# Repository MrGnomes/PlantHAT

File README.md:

<meta name='keywords' content='plantHAT, HAT, raspberry pi HAT, pi, IoT, app, python, raspberry pi, plant, plants, watering, automated greenhouse, pi watering plants'>

# PlantHAT

Python library and design files for a modular plant monitoring and watering system based on the Raspberry Pi.

It is powered by a 12V power supply an it backpowers the Pi so that everything can be run from a single supply.
The 12V can be used to power up to 5 additional 12V inductive loads, like water pumps or magnetic valves that can be controlled over 
the GPIO Pins of the Pi.

# Sensors

Connect a 3 Wire temperature/humidity sensor (e.g. DHT22) and up to 4 I2C sensors to monitor your plants.

# Hardware

You can find the schematic design file in the "hardware" section of this repo.

## Maximum Ratings
The HAT is designed to work with a single power supply, that backpowers the raspberry pi with 5V/2A.

Input Voltage: 12V 

# Python3 Web-APP (Flask)

## Windows
The App was written using the current Python Tool for Visual Studio included in the community edition of Visual Studio 2017 and as an extension for Visual Studio 2015.
If you have the GitHub extension for Visual Studio and the python tools installed you can clone the git and start right away by using the solution file.

By using the Visual Studio as the IDE, the flask based WebApp can be compiled and debugged on the windows development PC.
When the code is working, the app can be run inside the Pi and by using the PTVSD package one can remotely debug the flask app directly from the VS-IDE by attaching to the running process using the IP-Address of the Pi.
Python 3.4 (32-bit) was used, because this was the current python version supported by the Pi, when I started the project.

## Linux

If you are using linux, just clone the repo, install the required packages and run the app by typing:
>> python3 run.py

inside the app folder.

(requirements.txt file is coming soon)

## Screenshot

This is what the current working App looks like:

# Coming Soon - Sensor data charts and GPIO control

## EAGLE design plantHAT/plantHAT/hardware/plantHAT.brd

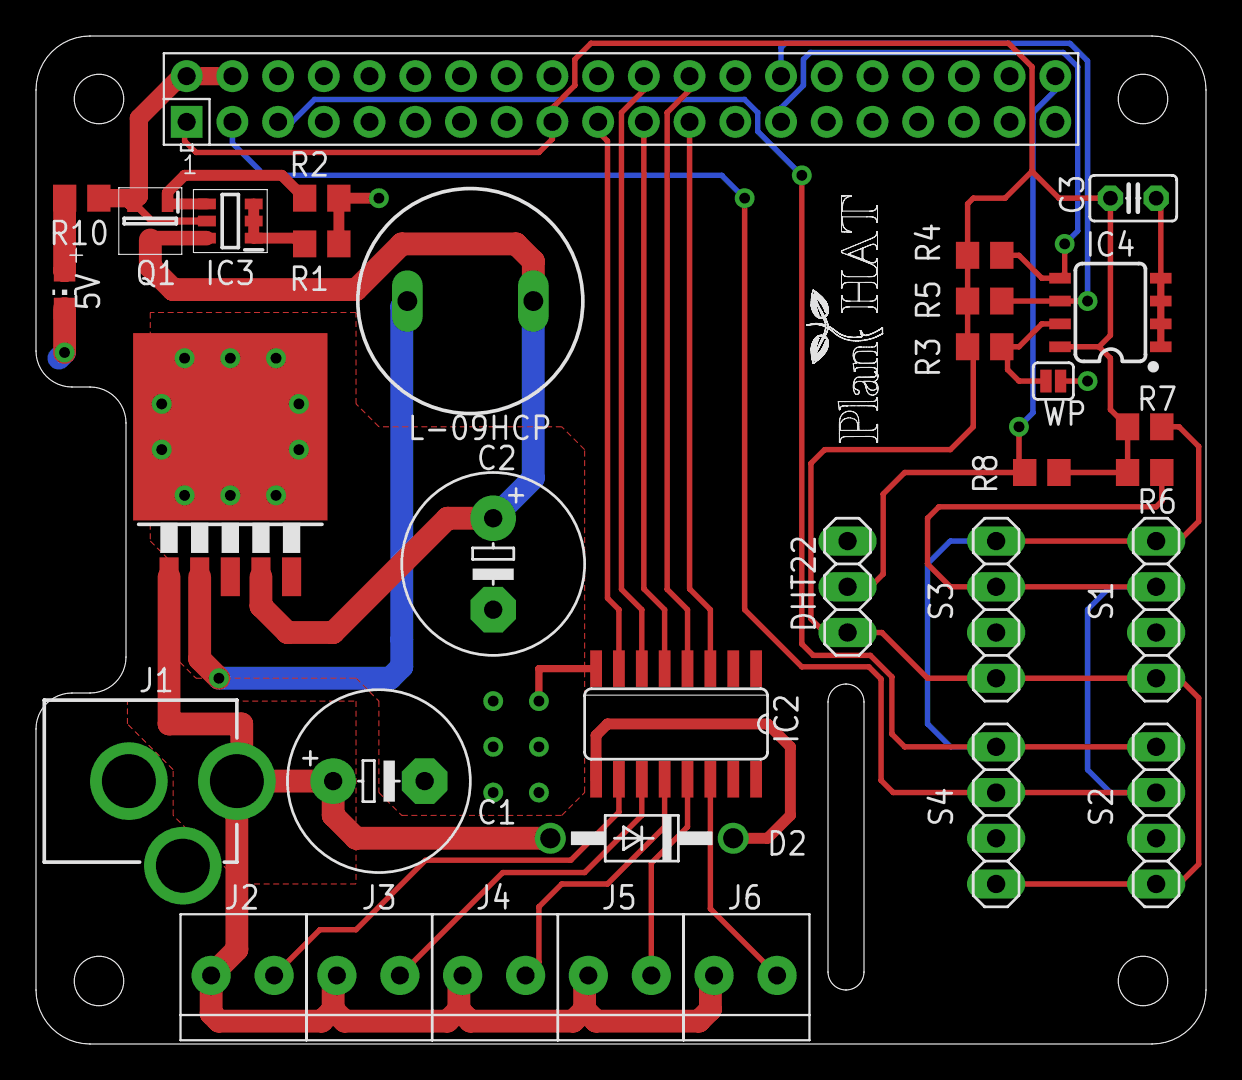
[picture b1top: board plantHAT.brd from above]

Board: 2 copper layers, 65.0 x 56.0 mm, 34 parts (1 on the bottom side), 26 nets.

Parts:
C1: 330u/35V; E5-10,5
C2: 180u; E5-10,5
C3: 100n; C025-025X050
D2: 1N4007; DO41-10
D3: B340A; SMA-DIODE
DHT22: 1X03
IC1: TO263-5
IC2: ULN2003AD; SO16
IC3: DMMT5401-7-F; SOT95P275X110-6N
IC4: 24LC256; SO08
J1: 12V; POWER_JACK_PTH
J2, J3, J4, J5, J6: 1X2-3.5MM
JP1: WP; SMT-JUMPER_2_NO_SILK
L2: 5V; CHIP-LED0805
L-09HCP: 68u; SD12-680
Q1: DMG2305UX-7; SOT96P240X100-3N
R1, R6, R7, R8: 10k; R0805
R2: 47k; R0805
R3, R4: 3,9k; R0805
R5: 3,8k; R0805
R10: 330; R0805
S1, S2, S3, S4: 1X04
X2: RASPI_BOARD_B+#_HDC; RASPI_BOARD_B+HAT_DF_CF

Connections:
3.3V: C3.1, DHT22.1, IC4.8, R3.2, R4.2, R5.2, R6.2, R7.2, R8.2, S1.1, S2.1, S3.1, S4.1, X2.1, X2.17
5V: IC3.5, Q1.2, R10.2, X2.2, X2.4
5V_PRE: C2.+, IC1.4, IC3.6, L-09HCP.2, Q1.3
12V: C1.+, D2.A, IC1.1, J1.PWR, J2.2, J3.2, J4.2, J5.2, J6.2
GND: C1.-, C2.-, C3.2, D3.A, DHT22.3, IC1.3, IC1.5, IC1.6, IC2.8, IC4.1, IC4.2, IC4.3, IC4.4, J1.GND, J1.GNDBREAK, JP1.1, L2.C, R1.2, R2.1, S1.2, S2.2, S3.2, S4.2, X2.6, X2.9, X2.14, X2.20, X2.25, X2.39
ID_SC: IC4.6, R5.1, X2.28
ID_SD: IC4.5, R4.1, X2.27
unnamed: D3.C, IC1.2, L-09HCP.1
unnamed: IC2.14, J6.1
unnamed: IC2.13, J5.1
unnamed: IC2.12, J4.1
unnamed: IC2.11, J3.1
unnamed: IC2.10, J2.1
unnamed: IC3.1, IC3.2, IC3.3, R1.1
unnamed: IC3.4, Q1.1, R2.2
unnamed: IC4.7, JP1.2, R3.1
unnamed: L2.A, R10.1
unnamed: D2.C, IC2.9
SCL: R7.1, S1.4, S2.4, S3.4, S4.4, X2.5
SDA: R6.1, S1.3, S2.3, S3.3, S4.3, X2.3
SENS_1: DHT22.2, R8.1, X2.40
ULN_3: IC2.3, X2.23
ULN_4: IC2.4, X2.24
ULN_5: IC2.5, X2.21
ULN_6: IC2.6, X2.22
ULN_7: IC2.7, X2.19

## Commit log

2017-04-24 Added Eagle layout and schematic.
2017-04-24 Initial Commit.
2017-04-24 Added schematic.
2017-05-17 Added the landing page for app. Added a loging an registration page to create local accounts. Added a dashboard with the basic style and functionality.
2017-05-17 Changed script inclusion in dashboard

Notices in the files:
parts and their libraries:
SparkFun-IC-Memory: Licensing: Creative Commons ShareAlike 4.0 International - https://creativecommons.org/licenses/by-sa/4.0
